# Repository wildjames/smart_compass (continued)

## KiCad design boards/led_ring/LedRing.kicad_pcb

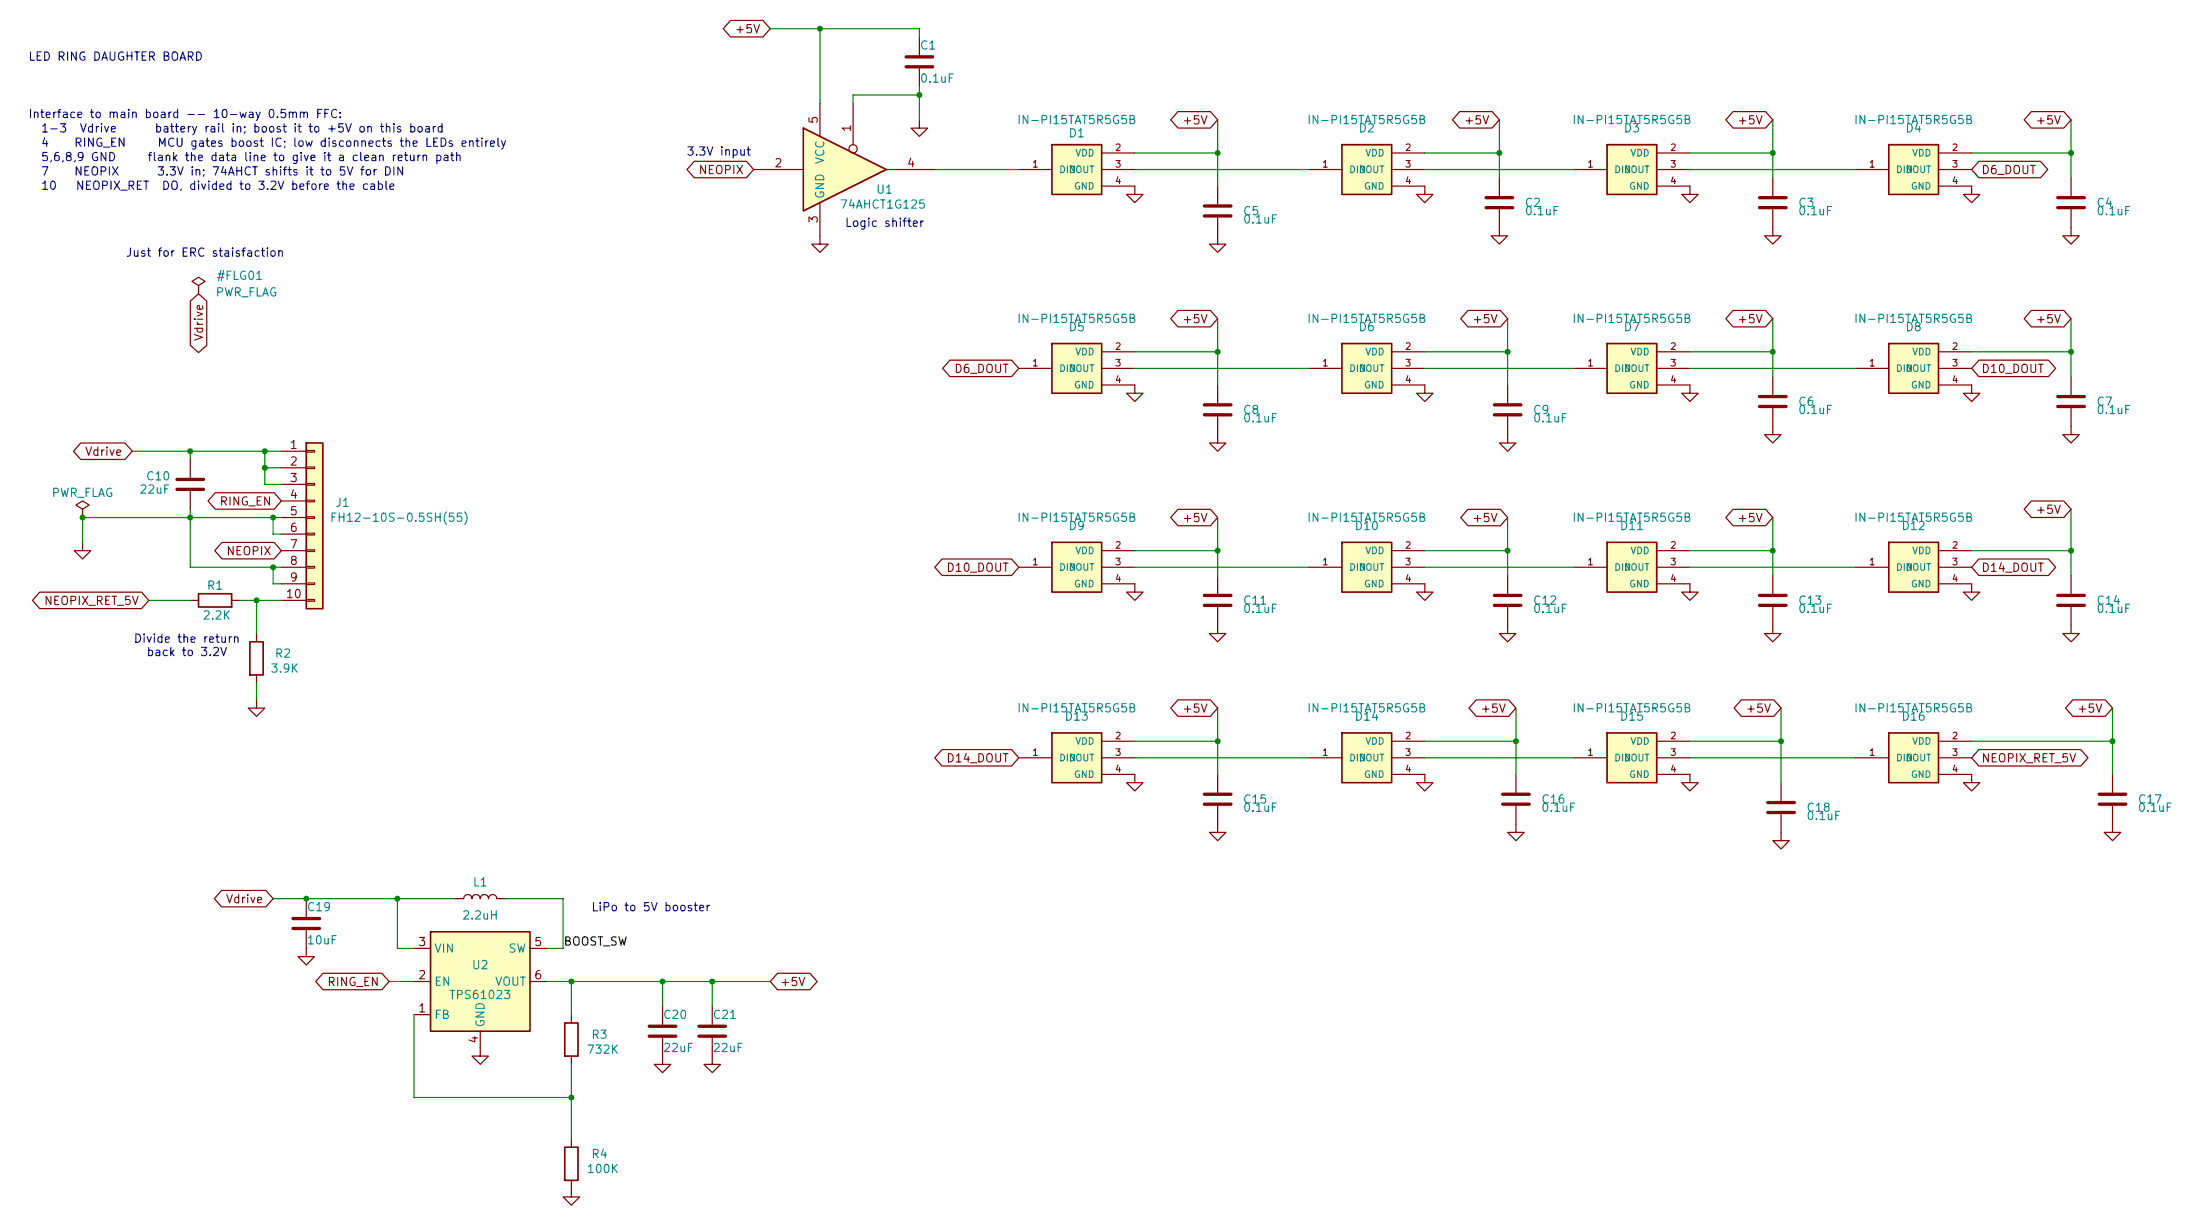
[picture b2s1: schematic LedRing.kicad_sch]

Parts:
C1, C2, C3, C4, C5, C6, C7, C8, C9, C11, C12, C13, C14, C15, C16, C17, C18: 0.1uF; C_0402_1005Metric; Voltage 16V; MPN CL05B104KO5VPNC; DigiKey_PN 1276-6844-1-ND
C10, C20, C21: 22uF; C_0805_2012Metric; Voltage 10V; MPN CL21A226KPCLRNC; DigiKey_PN 1276-6786-1-ND
C19: 10uF; C_0805_2012Metric; Voltage 10V; MPN CGA4J3X5R1A106K125AB; DigiKey_PN 445-6970-1-ND
D1, D2, D3, D4, D5, D6, D7, D8, D9, D10, D11, D12, D13, D14, D15, D16: IN-PI15TAT5R5G5B; LED_Inolux_IN-PI15TAT5R5G5B_1515; MPN IN-PI15TAT5R5G5B; DigiKey_PN 1830-IN-PI15TAT5R5G5BCT-ND
J1: FH12-10S-0.5SH(55); Hirose_FH12-10S-0.5SH_1x10-1MP_P0.50mm_Horizontal; MPN FH12-10S-0.5SH(55); DigiKey_PN HFJ110CT-ND
L1: 2.2uH; L_1008_2520Metric; MPN DFE252010F-2R2M=P2; DigiKey_PN 490-13042-1-ND
R1: 2.2K; R_0603_1608Metric; Tolerance 1%; MPN RC0603FR-072K2L; DigiKey_PN 311-2.20KHRCT-ND
R2: 3.9K; R_0603_1608Metric; Tolerance 1%; MPN RC0603FR-073K9L; DigiKey_PN 311-3.90KHRCT-ND
R3: 732K; R_0603_1608Metric; Tolerance 1%; MPN RC0603FR-07732KL; DigiKey_PN 311-732KHRCT-ND
R4: 100K; R_0603_1608Metric; Tolerance 1%; MPN RC0603FR-07100KL; DigiKey_PN 311-100KHRCT-ND
U1: 74AHCT1G125; SOT-23-5; MPN SN74AHCT1G125DBVR; DigiKey_PN 296-4708-1-ND
U2: TPS61023; SOT-563; MPN TPS61023DRLR; DigiKey_PN 296-TPS61023DRLRCT-ND

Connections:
+5V: C1.1, C2.1, C3.1, C4.1, C5.1, C6.1, C7.1, C8.1, C9.1, C11.1, C12.1, C13.1, C14.1, C15.1, C16.1, C17.1, C18.1, C20.1, C21.1, D1.2 (VDD), D2.2 (VDD), D3.2 (VDD), D4.2 (VDD), D5.2 (VDD), D6.2 (VDD), D7.2 (VDD), D8.2 (VDD), D9.2 (VDD), D10.2 (VDD), D11.2 (VDD), D12.2 (VDD), D13.2 (VDD), D14.2 (VDD), D15.2 (VDD), D16.2 (VDD), R3.1, U1.5 (VCC), U2.6 (VOUT)
D6_DOUT: D4.3 (DOUT), D5.1 (DIN)
D10_DOUT: D8.3 (DOUT), D9.1 (DIN)
D14_DOUT: D12.3 (DOUT), D13.1 (DIN)
GND: C1.2, C2.2, C3.2, C4.2, C5.2, C6.2, C7.2, C8.2, C9.2, C10.2, C11.2, C12.2, C13.2, C14.2, C15.2, C16.2, C17.2, C18.2, C19.2, C20.2, C21.2, D1.4 (GND), D2.4 (GND), D3.4 (GND), D4.4 (GND), D5.4 (GND), D6.4 (GND), D7.4 (GND), D8.4 (GND), D9.4 (GND), D10.4 (GND), D11.4 (GND), D12.4 (GND), D13.4 (GND), D14.4 (GND), D15.4 (GND), D16.4 (GND), J1.5, J1.6, J1.8, J1.9, R2.2, R4.2, U1.1, U1.3 (GND), U2.4 (GND)
NEOPIX: J1.7, U1.2
NEOPIX_RET_5V: D16.3 (DOUT), R1.1
unnamed: D1.1 (DIN), U1.4
unnamed: D1.3 (DOUT), D2.1 (DIN)
unnamed: D2.3 (DOUT), D3.1 (DIN)
unnamed: D3.3 (DOUT), D4.1 (DIN)
unnamed: D5.3 (DOUT), D6.1 (DIN)
unnamed: D6.3 (DOUT), D7.1 (DIN)
unnamed: D7.3 (DOUT), D8.1 (DIN)
unnamed: D9.3 (DOUT), D10.1 (DIN)
unnamed: D10.3 (DOUT), D11.1 (DIN)
unnamed: D11.3 (DOUT), D12.1 (DIN)
unnamed: D13.3 (DOUT), D14.1 (DIN)
unnamed: D14.3 (DOUT), D15.1 (DIN)
unnamed: D15.3 (DOUT), D16.1 (DIN)
unnamed: J1.10, R1.2, R2.1
unnamed: R3.2, R4.1, U2.1 (FB)
unnamed: L1.2, U2.5 (SW)
RING_EN: J1.4, U2.2 (EN)
Vdrive: C10.1, C19.1, J1.1, J1.2, J1.3, L1.1, U2.3 (VIN)

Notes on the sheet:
5,6,8,9 GND flank the data line to give it a clean return path
Just for ERC staisfaction
Logic shifter
Divide the return back to 3.2V
4 RING_EN MCU gates boost IC; low disconnects the LEDs entirely
7 NEOPIX 3.3V in; 74AHCT shifts it to 5V for DIN
Interface to main board -- 10-way 0.5mm FFC:
3.3V input
1-3 Vdrive battery rail in; boost it to +5V on this board
10 NEOPIX_RET DO, divided to 3.2V before the cable
LED RING DAUGHTER BOARD
LiPo to 5V booster

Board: 2 copper layers, 45 parts (0 on the bottom side), 25 nets, no tracks yet.

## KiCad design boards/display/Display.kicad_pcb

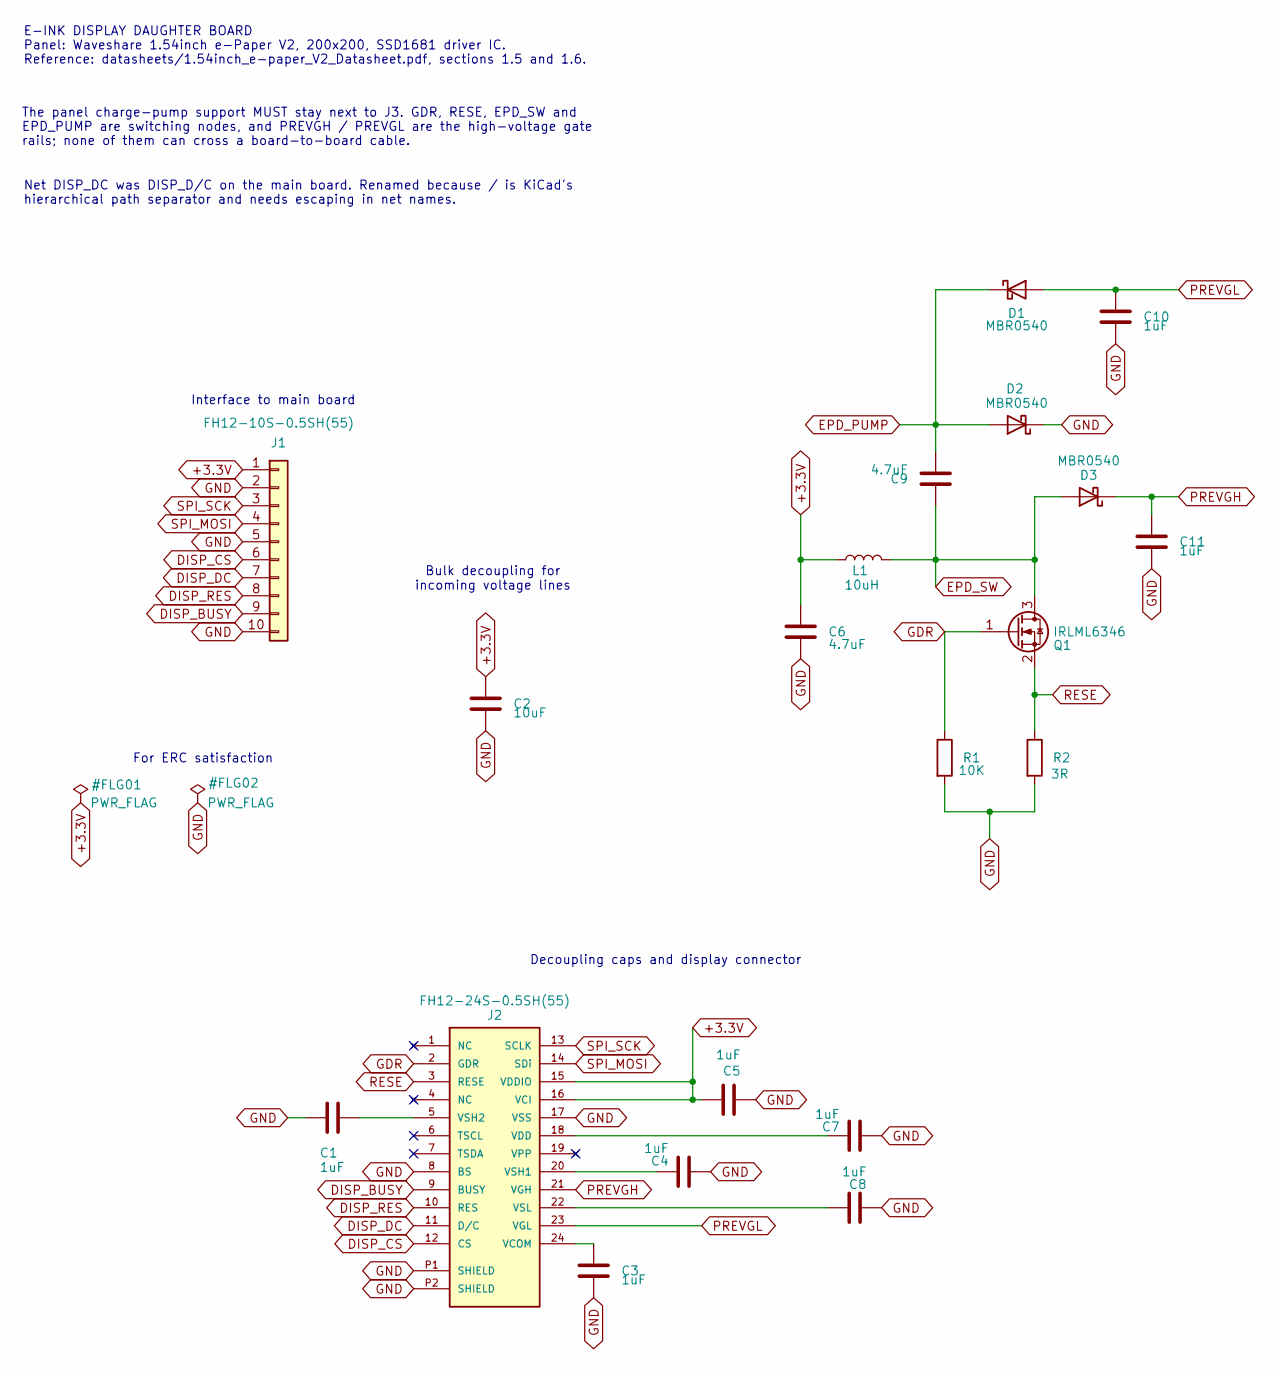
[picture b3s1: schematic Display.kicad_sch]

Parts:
C1, C3, C4, C5, C7, C8, C10, C11: 1uF; C_0603_1608Metric; Voltage 50V; Tolerance 10%; MPN C1608X7R1H105K080AB; DigiKey_PN 445-C1608X7R1H105K080ABCT-ND
C2: 10uF; C_0805_2012Metric; Voltage 10V; MPN CGA4J3X5R1A106K125AB; DigiKey_PN 445-6970-1-ND
C6, C9: 4.7uF; C_1206_3216Metric; Voltage 50V; Tolerance 10%; MPN CL31B475KBHNFNE; DigiKey_PN 1276-3179-1-ND
D1, D2, D3: MBR0540; D_SOD-123; MPN MBR0540-TP; DigiKey_PN MBR0540TPMSCT-ND
J1: FH12-10S-0.5SH(55); Hirose_FH12-10S-0.5SH_1x10-1MP_P0.50mm_Horizontal; MPN FH12-10S-0.5SH(55); DigiKey_PN HFJ110CT-ND
J2: FH12-24S-0.5SH(55); HRS_FH12-24S-0.5SH_55_; MPN FH12-24S-0.5SH(55); DigiKey_PN HFJ124CT-ND
L1: 10uH; L_Bourns_SRN3015BTA; MPN SRN3015BTA-100M; DigiKey_PN 118-SRN3015BTA-100MCT-ND
Q1: IRLML6346; SOT-23; MPN IRLML6346TRPBF; DigiKey_PN IRLML6346TRPBFCT-ND
R1: 10K; R_0603_1608Metric; Tolerance 1%; MPN RC0603FR-0710KL; DigiKey_PN 311-10.0KHRCT-ND
R2: 3R; R_0603_1608Metric; Tolerance 1%; MPN RC0603FR-073RL; DigiKey_PN 13-RC0603FR-073RLCT-ND

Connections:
+3.3V: C2.1, C5.1, C6.1, J1.1, J2.15 (VDDIO), J2.16 (VCI), L1.1
DISP_BUSY: J1.9, J2.9 (BUSY)
DISP_CS: J1.6, J2.12 (CS)
DISP_DC: J1.7, J2.11 (D/C)
DISP_RES: J1.8, J2.10 (RES)
EPD_PUMP: C9.2, D1.1 (K), D2.2 (A)
EPD_SW: C9.1, D3.2 (A), L1.2, Q1.3 (D)
GDR: J2.2 (GDR), Q1.1 (G), R1.1
GND: C1.2, C2.2, C3.2, C4.2, C5.2, C6.2, C7.2, C8.2, C10.2, C11.2, D2.1 (K), J1.2, J1.5, J1.10, J2.8 (BS), J2.17 (VSS), J2.P1 (SHIELD), J2.P2 (SHIELD), R1.2, R2.2
unnamed: C3.1, J2.24 (VCOM)
unnamed: C7.1, J2.18 (VDD)
unnamed: C4.1, J2.20 (VSH1)
unnamed: C1.1, J2.5 (VSH2)
unnamed: C8.1, J2.22 (VSL)
PREVGH: C11.1, D3.1 (K), J2.21 (VGH)
PREVGL: C10.1, D1.2 (A), J2.23 (VGL)
RESE: J2.3 (RESE), Q1.2 (S), R2.1
SPI_MOSI: J1.4, J2.14 (SDi)
SPI_SCK: J1.3, J2.13 (SCLK)

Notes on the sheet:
Net DISP_DC was DISP_D/C on the main board. Renamed because / is KiCad's
E-INK DISPLAY DAUGHTER BOARD
Decoupling caps and display connector
The panel charge-pump support MUST stay next to J3. GDR, RESE, EPD_SW and
rails; none of them can cross a board-to-board cable.
Reference: datasheets/1.54inch_e-paper_V2_Datasheet.pdf, sections 1.5 and 1.6.
For ERC satisfaction
EPD_PUMP are switching nodes, and PREVGH / PREVGL are the high-voltage gate
Bulk decoupling for incoming voltage lines
Panel: Waveshare 1.54inch e-Paper V2, 200x200, SSD1681 driver IC.
Interface to main board
hierarchical path separator and needs escaping in net names.

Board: 4 copper layers, 20 parts (0 on the bottom side), 19 nets, no tracks yet.

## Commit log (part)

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2026-05-27 Schematic in a good place. IMU, GNSS, LoRa, lipo charging and usb, and neopixels all in.
2026-05-27 Double checked capacitor values and footprints
2026-05-27 Remove unused project
2026-05-28 More fiddling. Added 3D models to the components
2026-05-28 Categorise pcb layout by specsheet boxes
2026-05-28 README
2026-05-28 TODO list
2026-05-28 migrating to nRF controller
2026-05-29 Migrate to the nRF microcontroller. Attempt to implement my own lora section - will probably remove later.
2026-05-30 Start PCB design again - compact requirements
2026-05-31 Main board design is in place. Needs haptics and buzzer
2026-05-31 v1.0 pcb design
2026-05-31 Some notes. Figuring out costs
2026-06-02 Wrote some more readme stuff. Added haptics to the schematic
2026-06-02 Update the board components, and assign footprints and BOM stuff to haptics
2026-06-02 Added flash memory
2026-06-02 wire up the eink connector
2026-06-04 Move to hierarchical schematic
2026-06-04 Some minor cleaning
2026-06-04 Archive the version of the schematic I submitted to reddit
2026-06-05 review bom and footprints
2026-06-05 Check over i2c, spi, and uart connections
2026-06-09 Re-did the layout and routing for the whole board. Added more LEDs, haptics, and properly modelled the e-ink display
2026-06-09 populate the board components file with the current design
2026-06-09 cleanup of board traces
2026-06-09 Rename project in kicad
2026-06-09 update user interactions
2026-06-09 Start the basic foundation for the rust code
2026-06-09 user flows
2026-06-11 Update pcb
2026-06-12 some small changes
2026-06-12 make a note on batteries
2026-06-16 minor start of framework sketch
2026-06-16 pcb changes
2026-06-16 Scaffolding the firmware. Starting with a mock fuel gauge
2026-06-17 Some scaffolding with the rust code
2026-06-17 Allow dead code for now, and update devcontainer to be able to build the cargo project
2026-06-17 successful builds. cargo fmt
2026-06-17 Make into a library
2026-06-17 Create a simulator for playing around with the firmware. Make some changes to the firmware to accomodate this, and also slightly refactor how it handles stuff to make it more extensible
2026-06-18 Use millis for durations
2026-06-18 plan out a web interface for the sim
